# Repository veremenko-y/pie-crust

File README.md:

# Aplle II Pie Crust Card

WIP storage/serial card

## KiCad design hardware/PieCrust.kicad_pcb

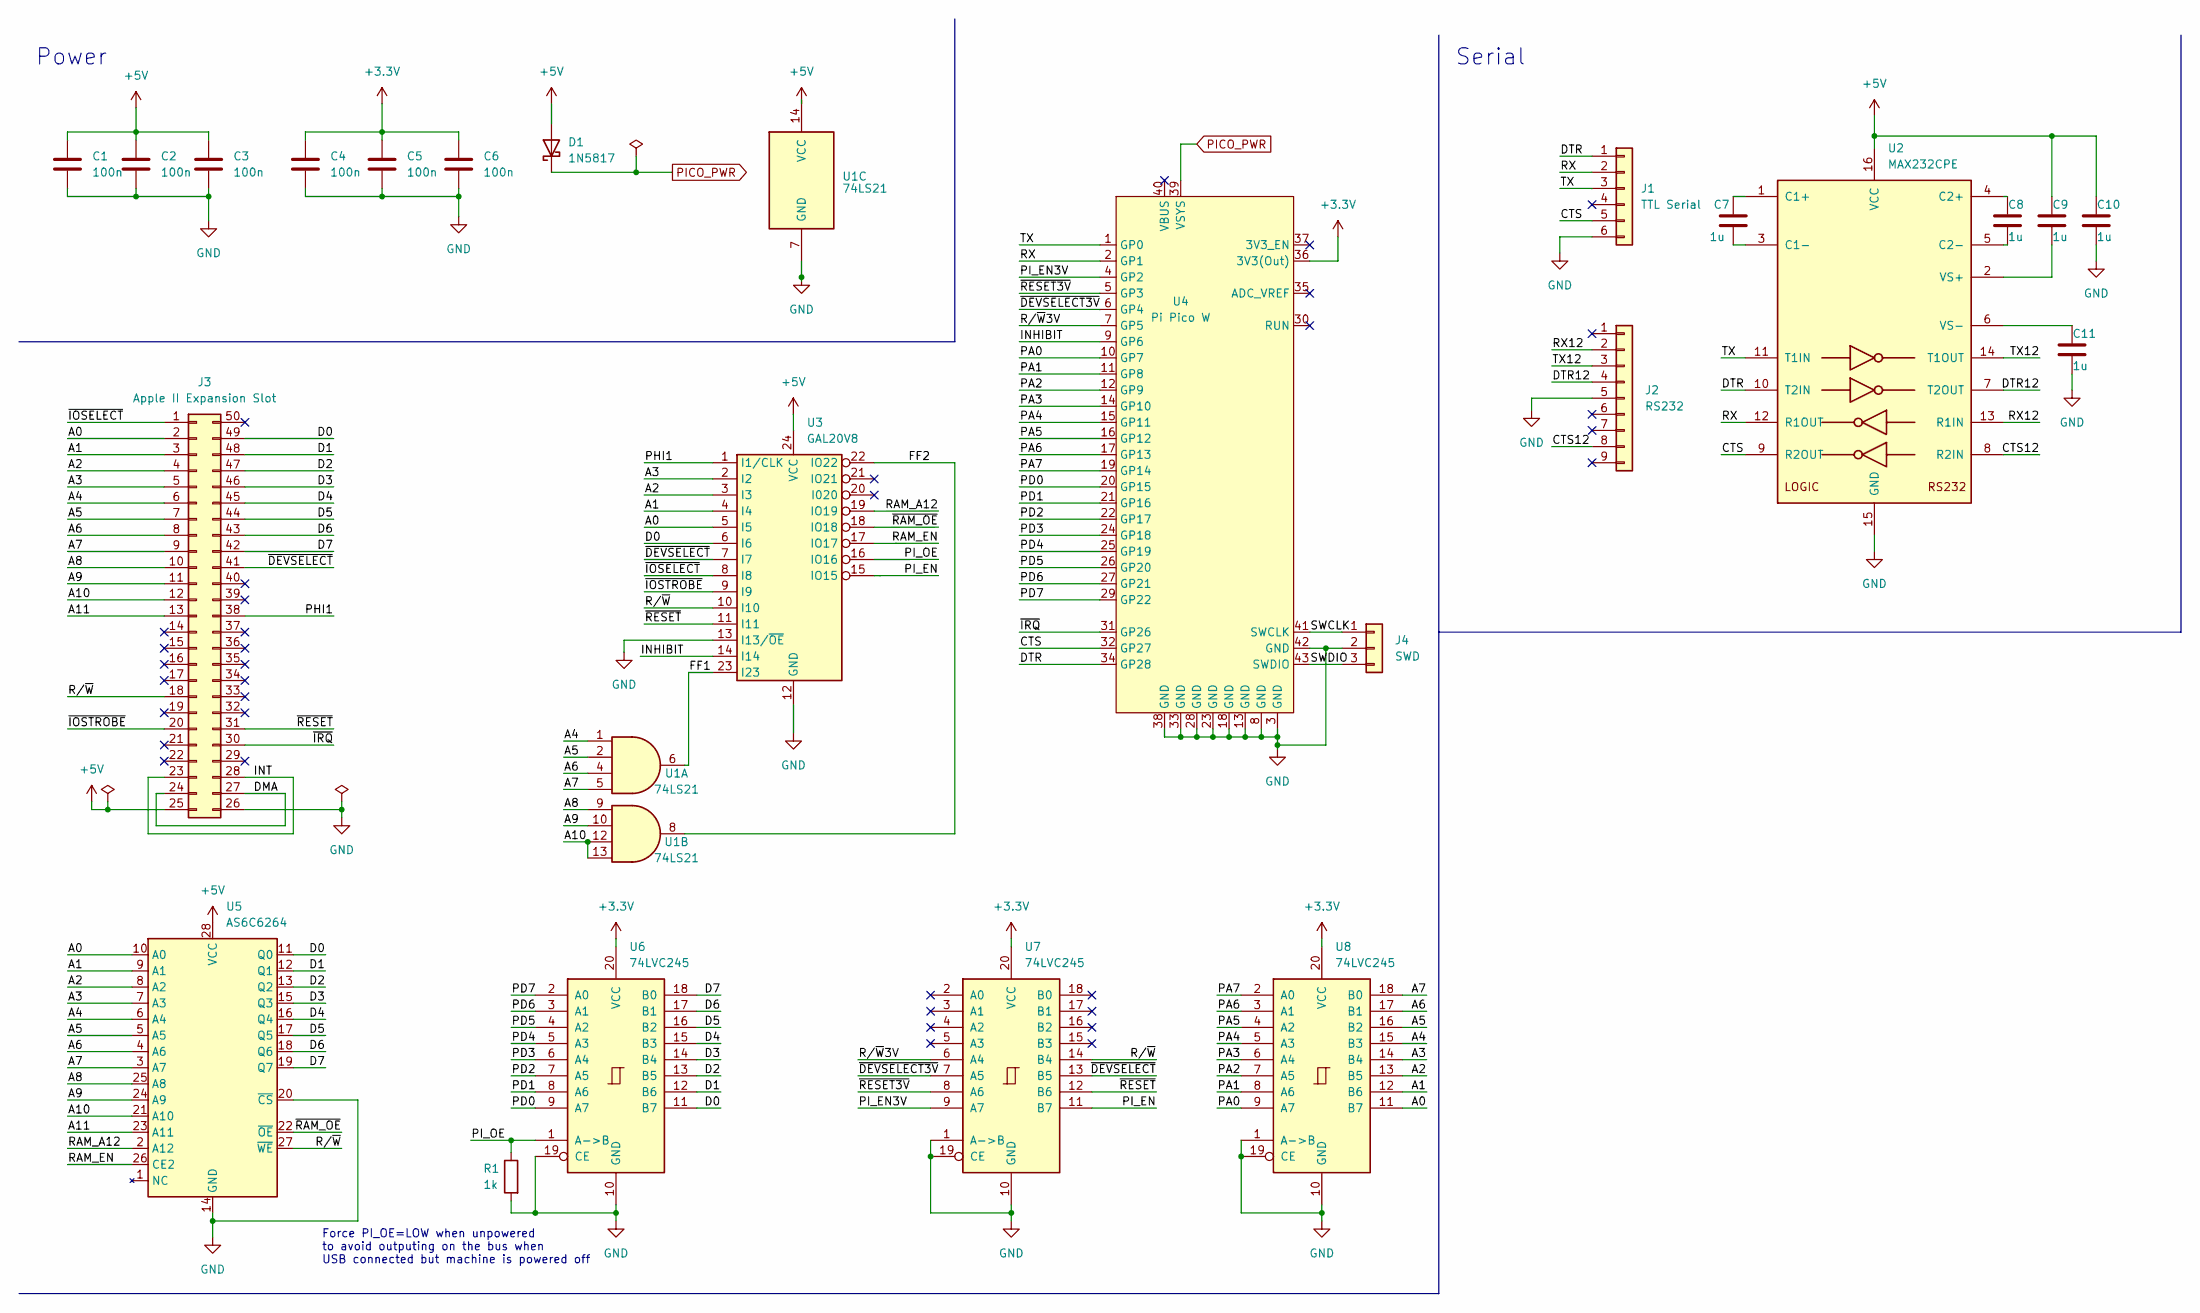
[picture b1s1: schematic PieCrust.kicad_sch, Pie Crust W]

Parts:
C1, C2, C3, C4, C5, C6: 100n; C_Disc_D4.3mm_W1.9mm_P5.00mm
C7, C8, C9, C10, C11: 1u; C_Disc_D4.3mm_W1.9mm_P5.00mm
D1: 1N5817; D_DO-41_SOD81_P10.16mm_Horizontal
J1: TTL Serial; PinHeader_1x06_P2.54mm_Vertical
J2: RS232; PinHeader_2x05_RS232
J3: Apple II Expansion Slot; Apple II Expansion Edge Connector
J4: SWD; PinHeader_1x03_P2.54mm_Vertical
R1: 1k; R_Axial_DIN0204_L3.6mm_D1.6mm_P5.08mm_Horizontal
U1: 74LS21; DIP-14_W7.62mm_Socket
U2: MAX232CPE; DIP-16_W7.62mm_Socket
U3: GAL20V8; DIP-24_W7.62mm_Socket
U4: Pi Pico W; Pi Pico W Socket_Comb
U5: AS6C6264; DIP-28_W15.24mm_Socket
U6, U7, U8: 74LVC245; DIP-20_W7.62mm_Socket

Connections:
+3.3V: C4.1, C5.1, C6.1, U4.36 (3V3(Out)), U6.20 (VCC), U7.20 (VCC), U8.20 (VCC)
+5V: C1.1, C2.1, C3.1, C9.1, C10.1, D1.2 (A), J3.25, U1.14 (VCC), U2.16 (VCC), U3.24 (VCC), U5.28 (VCC)
/A0: J3.2, U3.5 (I5), U5.10 (A0), U8.11 (B7)
/A1: J3.3, U3.4 (I4), U5.9 (A1), U8.12 (B6)
/A2: J3.4, U3.3 (I3), U5.8 (A2), U8.13 (B5)
/A3: J3.5, U3.2 (I2), U5.7 (A3), U8.14 (B4)
/A4: J3.6, U1.1, U5.6 (A4), U8.15 (B3)
/A5: J3.7, U1.2, U5.5 (A5), U8.16 (B2)
/A6: J3.8, U1.4, U5.4 (A6), U8.17 (B1)
/A7: J3.9, U1.5, U5.3 (A7), U8.18 (B0)
/A8: J3.10, U1.9, U5.25 (A8)
/A9: J3.11, U1.10, U5.24 (A9)
/A10: J3.12, U1.12, U1.13, U5.21 (A10)
/A11: J3.13, U5.23 (A11)
/CTS: J1.5, U2.9 (R2OUT), U4.32 (GP27)
/CTS12: J2.8, U2.8 (R2IN)
/D0: J3.49, U3.6 (I6), U5.11 (Q0), U6.11 (B7)
/D1: J3.48, U5.12 (Q1), U6.12 (B6)
/D2: J3.47, U5.13 (Q2), U6.13 (B5)
/D3: J3.46, U5.15 (Q3), U6.14 (B4)
/D4: J3.45, U5.16 (Q4), U6.15 (B3)
/D5: J3.44, U5.17 (Q5), U6.16 (B2)
/D6: J3.43, U5.18 (Q6), U6.17 (B1)
/D7: J3.42, U5.19 (Q7), U6.18 (B0)
/DMA: J3.24, J3.27
/DTR: J1.1, U2.10 (T2IN), U4.34 (GP28)
/DTR12: J2.4, U2.7 (T2OUT)
/FF1: U1.6, U3.23 (I23)
/FF2: U1.8, U3.22 (IO22)
/INHIBIT: U3.14 (I14), U4.9 (GP6)
/INT: J3.23, J3.28
/PA0: U4.10 (GP7), U8.9 (A7)
/PA1: U4.11 (GP8), U8.8 (A6)
/PA2: U4.12 (GP9), U8.7 (A5)
/PA3: U4.14 (GP10), U8.6 (A4)
/PA4: U4.15 (GP11), U8.5 (A3)
/PA5: U4.16 (GP12), U8.4 (A2)
/PA6: U4.17 (GP13), U8.3 (A1)
/PA7: U4.19 (GP14), U8.2 (A0)
/PD0: U4.20 (GP15), U6.9 (A7)
/PD1: U4.21 (GP16), U6.8 (A6)
/PD2: U4.22 (GP17), U6.7 (A5)
/PD3: U4.24 (GP18), U6.6 (A4)
/PD4: U4.25 (GP19), U6.5 (A3)
/PD5: U4.26 (GP20), U6.4 (A2)
/PD6: U4.27 (GP21), U6.3 (A1)
/PD7: U4.29 (GP22), U6.2 (A0)
/PHI1: J3.38, U3.1 (I1/CLK)
/PI_EN: U3.15 (IO15), U7.11 (B7)
/PI_EN3V: U4.4 (GP2), U7.9 (A7)
/PI_OE: R1.1, U3.16 (IO16), U6.1 (A->B)
/RAM_A12: U3.19 (IO19), U5.2 (A12)
/RAM_EN: U3.17 (IO17), U5.26 (CE2)
/RX: J1.2, U2.12 (R1OUT), U4.2 (GP1)
/RX12: J2.2, U2.13 (R1IN)
/R/~W: J3.18, U3.10 (I10), U5.27 (~WE), U7.14 (B4)
/R/~W3V: U4.7 (GP5), U7.6 (A4)
/SWCLK: J4.1, U4.41 (SWCLK)
/SWDIO: J4.3, U4.43 (SWDIO)
/TX: J1.3, U2.11 (T1IN), U4.1 (GP0)
/TX12: J2.3, U2.14 (T1OUT)
/~DEVSELECT3V: U4.6 (GP4), U7.7 (A5)
/~DEVSELECT: J3.41, U3.7 (I7), U7.13 (B5)
/~IOSELECT: J3.1, U3.8 (I8)
/~IOSTROBE: J3.20, U3.9 (I9)
/~IRQ: J3.30, U4.31 (GP26)
/~RAM_OE: U3.18 (IO18), U5.22 (~OE)
/~RESET3V: U4.5 (GP3), U7.8 (A6)
/~RESET: J3.31, U3.11 (I11), U7.12 (B6)
GND: C1.2, C2.2, C3.2, C4.2, C5.2, C6.2, C10.2, C11.2, J1.6, J2.5, J3.26, J4.2, R1.2, U1.7 (GND), U2.15 (GND), U3.12 (GND), U3.13 (I13/~OE), U4.3 (GND), U4.8 (GND), U4.13 (GND), U4.18 (GND), U4.23 (GND), U4.28 (GND), U4.33 (GND), U4.38 (GND), U4.42 (GND), U5.14 (GND), U5.20 (~CS), U6.10 (GND), U6.19 (CE), U7.1 (A->B), U7.10 (GND), U7.19 (CE), U8.1 (A->B), U8.10 (GND), U8.19 (CE)
unnamed: C7.1, U2.1 (C1+)
unnamed: C7.2, U2.3 (C1-)
unnamed: C8.1, U2.4 (C2+)
unnamed: C8.2, U2.5 (C2-)
unnamed: C9.2, U2.2 (VS+)
unnamed: C11.1, U2.6 (VS-)
PICO_PWR: D1.1 (K), U4.39 (VSYS)

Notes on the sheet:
Power
Force PI_OE=LOW when unpowered to avoid outputing on the bus when USB connected but machine is powered off
Serial

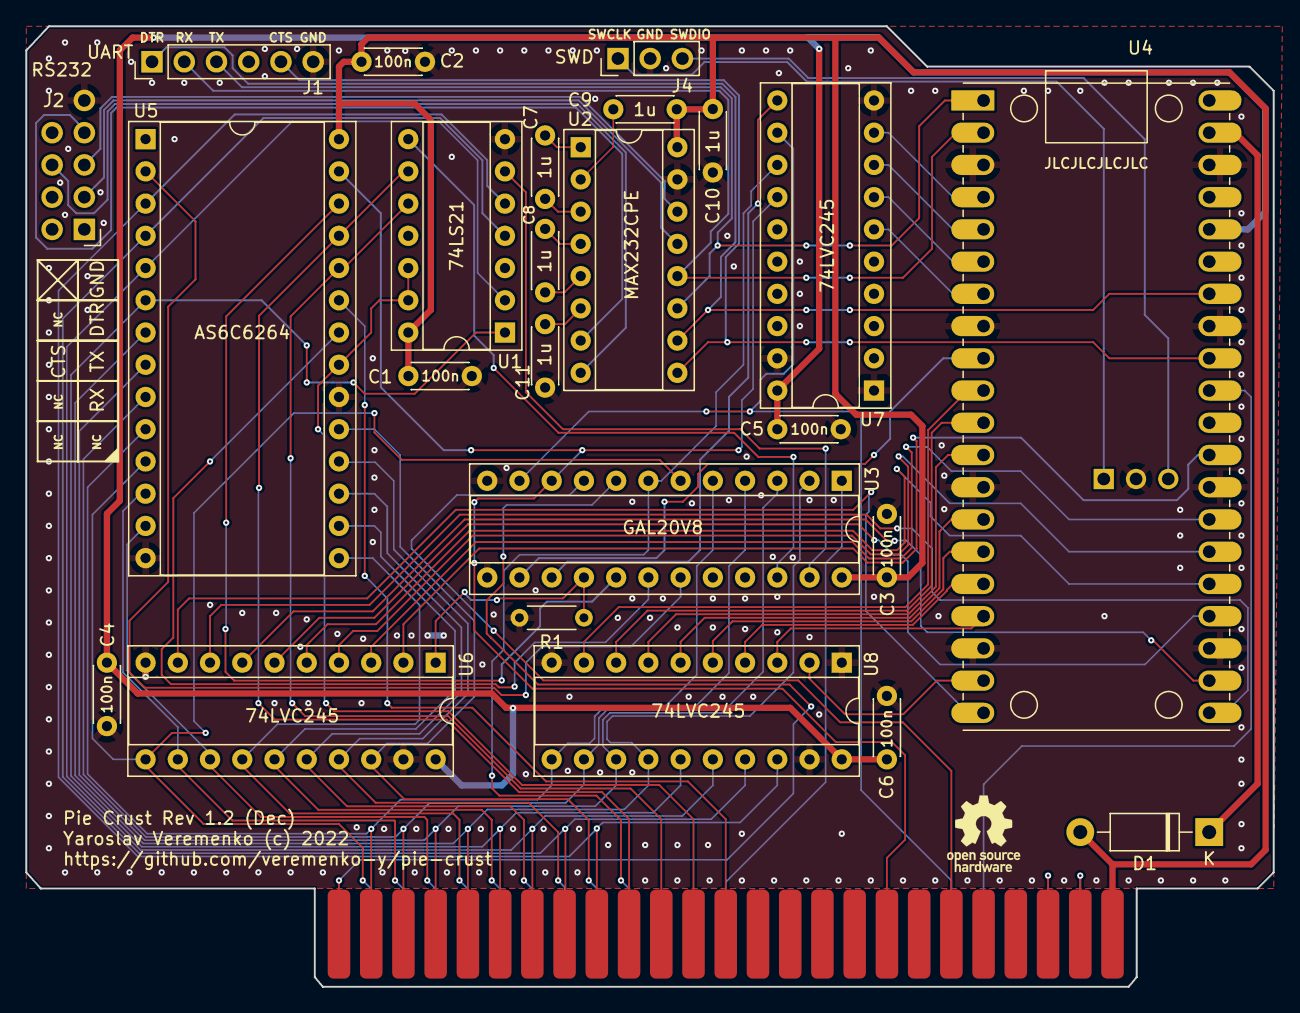
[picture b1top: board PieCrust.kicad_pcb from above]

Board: 2 copper layers, 98.3 x 75.7 mm, 25 parts (0 on the bottom side), 77 nets.

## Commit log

2023-03-25 Added README
2024-04-03 Possibility to run from ram excluding wifi firmware. Not tested

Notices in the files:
hardware/PieCrust.kicad_pcb:
Yaroslav Veremenko (c) 2022
